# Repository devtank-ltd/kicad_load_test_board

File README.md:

# kicad_load_test_board
A software controlled load test board for resistive load testing of products

Copyright Devtank Ltd 2019.

This documentation describes Open Hardware and is licensed under the CERN OHL v. 1.2.
You may redistribute and modify this documentation under the terms of the CERN OHL v.1.2. (http://ohwr.org/cernohl). This documentation is distributed WITHOUT ANY EXPRESS OR IMPLIED WARRANTY, INCLUDING OF MERCHANTABILITY, SATISFACTORY QUALITY AND FITNESS FOR A PARTICULAR PURPOSE. Please see the CERN OHL v.1.2 for applicable conditions

This folder contains the load test board hardware schematics and pcb layout files 

You will need Kicad to open hardware design files.

Test and measurement products can be purchased directly from Devtank Ltd.

Please contact:
Tim Telford
Technical Director - Devtank Ltd
+44 (0)1335 818014

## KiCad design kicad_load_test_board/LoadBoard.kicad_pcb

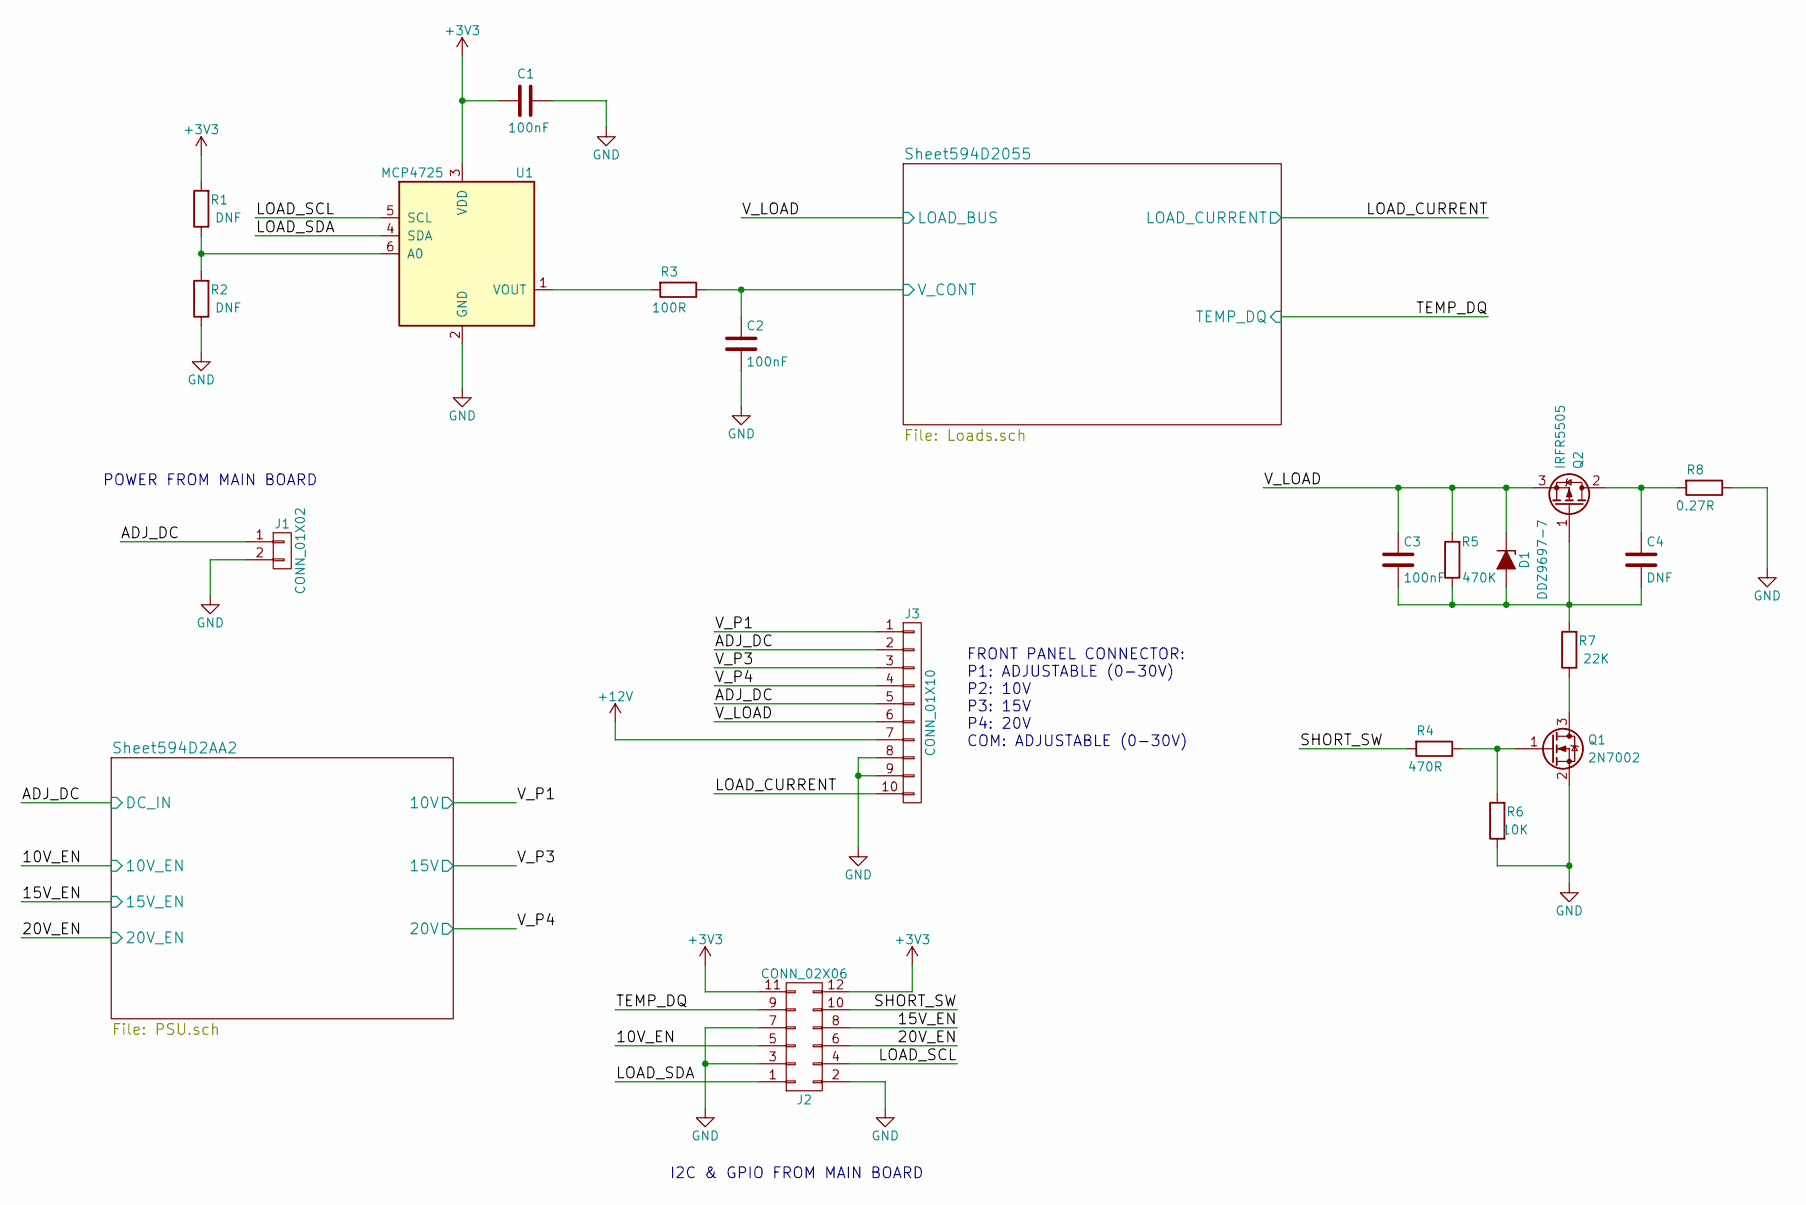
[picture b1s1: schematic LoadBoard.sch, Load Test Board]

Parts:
C1, C2, C3: 100nF; C_0603
C4: DNF; C_0603
D1: DDZ9697-7; D_SOD-123
J1: CONN_01X02; Molex_MiniFit-JR-5556-02A_2x01x4.20mm_Straight
J2: CONN_02X06; IDC_Header_Straight_12pins
J3: CONN_01X10; Molex_KK-6410-10_10x2.54mm_Straight
Q1: 2N7002; SOT-23
Q2: IRFR5505; TO-252-3_TabPin2
R1, R2: DNF; R_0603
R3: 100R; R_0603
R4: 470R; R_0603
R5: 470K; R_0603
R6: 10K; R_0603
R7: 22K; R_0603
R8: 0.27R; R_2816
U1: MCP4725; SOT-23-6

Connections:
+3V3: C1.2, J2.11, J2.12, R1.2, U1.3 (VDD); also elsewhere on the board
+12V: J3.7; also elsewhere on the board
/10V_EN: J2.5; also elsewhere on the board
/15V_EN: J2.8; also elsewhere on the board
/20V_EN: J2.6; also elsewhere on the board
/ADJ_DC: J1.1, J3.2, J3.5; also elsewhere on the board
/LOAD_CURRENT: J3.10; also elsewhere on the board
/LOAD_SCL: J2.4, U1.5 (SCL)
/LOAD_SDA: J2.1, U1.4 (SDA)
/SHORT_SW: J2.10, R4.2
/Sheet594D2055/V_CONT: C2.1, R3.1; also elsewhere on the board
/TEMP_DQ: J2.9; also elsewhere on the board
/V_LOAD: C3.1, D1.1 (K), J3.6, Q2.3 (S), R5.2; also elsewhere on the board
/V_P1: J3.1; also elsewhere on the board
/V_P3: J3.3; also elsewhere on the board
/V_P4: J3.4; also elsewhere on the board
GND: C1.1, C2.2, J1.2, J2.2, J2.3, J2.7, J3.8, J3.9, Q1.2 (S), R2.1, R6.1, R8.1, U1.2 (GND); also elsewhere on the board
unnamed: C3.2, C4.2, D1.2 (A), Q2.1 (G), R5.1, R7.2
unnamed: C4.1, Q2.2 (D), R8.2
unnamed: Q1.1 (G), R4.1, R6.2
unnamed: Q1.3 (D), R7.1
unnamed: R1.1, R2.2, U1.6 (A0)
unnamed: R3.2, U1.1 (VOUT)

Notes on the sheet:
POWER FROM MAIN BOARD
I2C & GPIO FROM MAIN BOARD
FRONT PANEL CONNECTOR: P1: ADJUSTABLE (0-30V) P2: 10V P3: 15V P4: 20V COM: ADJUSTABLE (0-30V)

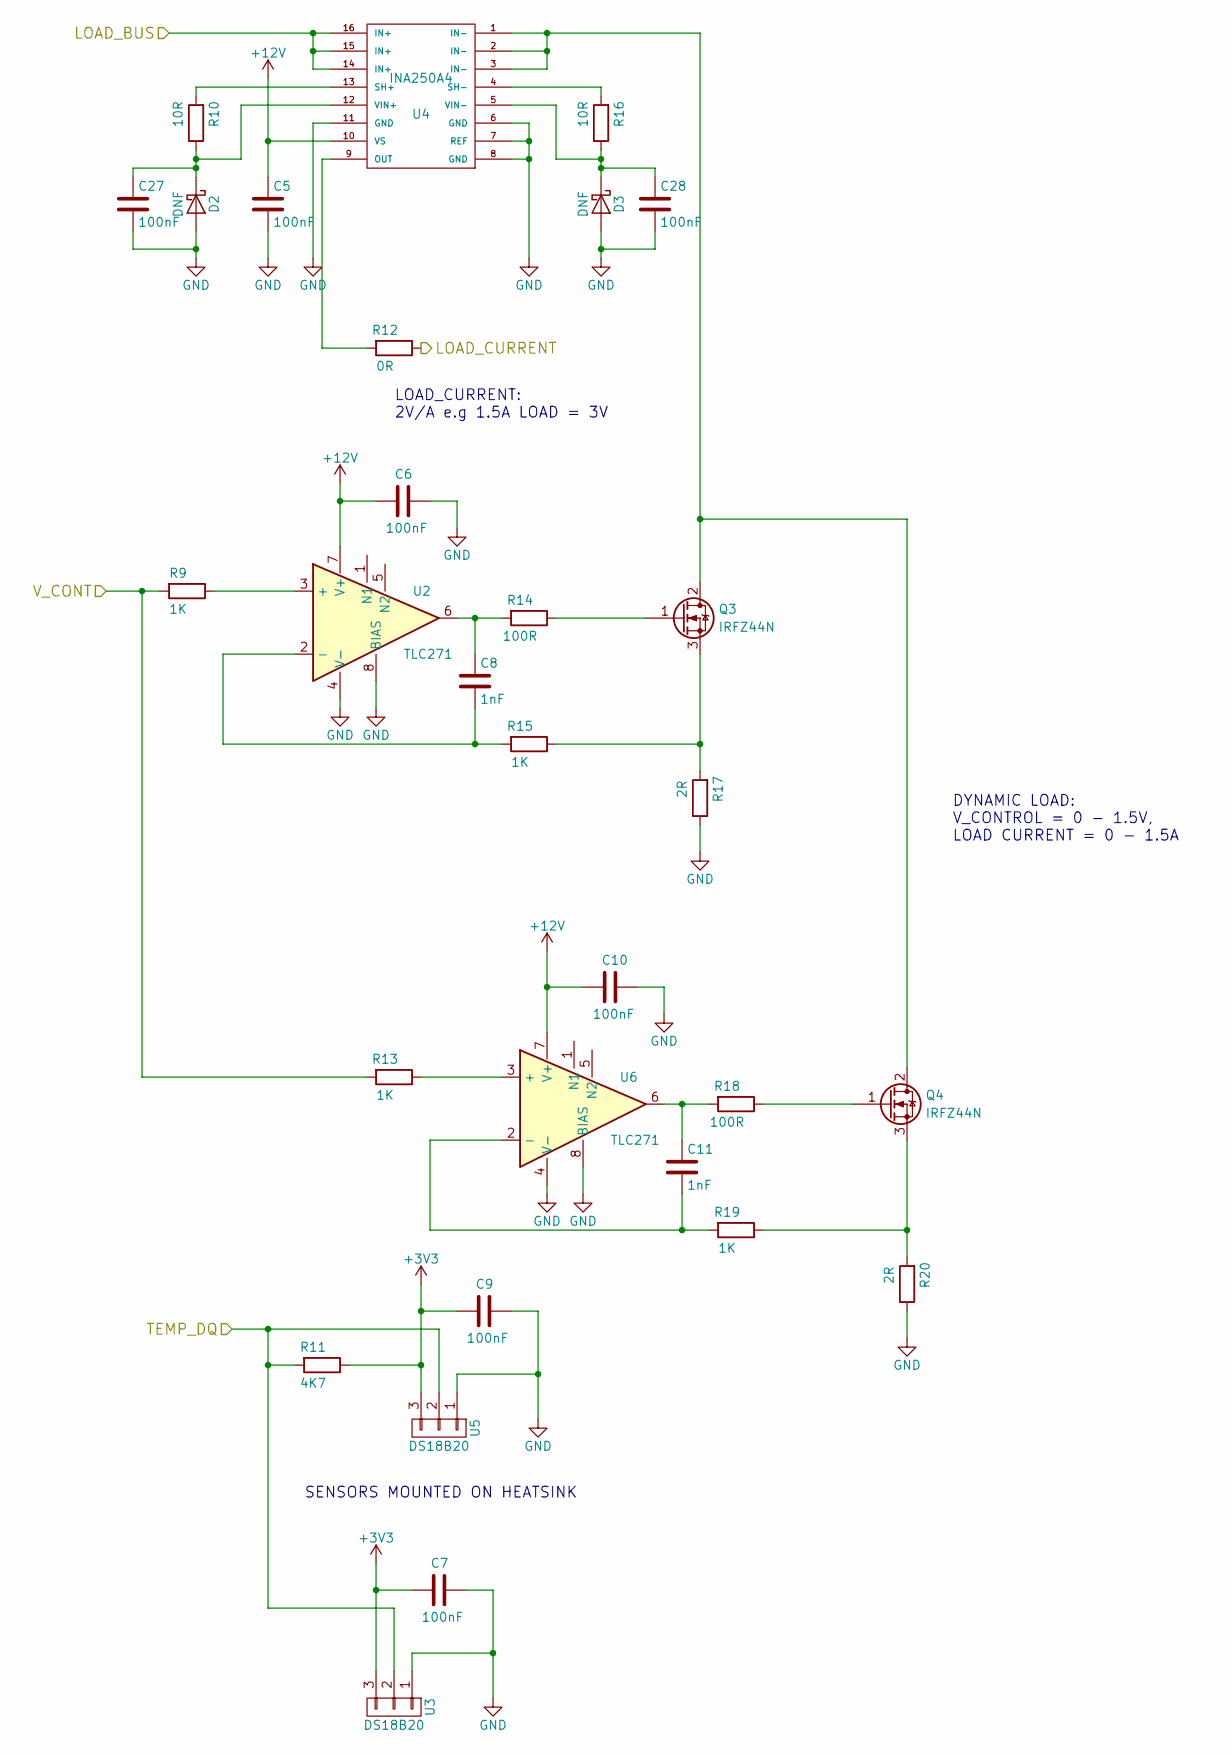
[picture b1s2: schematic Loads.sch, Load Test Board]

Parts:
C5, C6, C7, C9, C10, C27, C28: 100nF; C_0603
C8, C11: 1nF; C_0603
D2, D3: DNF; D_SOD-123
Q3, Q4: IRFZ44N; TO-220_Vertical
R9, R13, R15, R19: 1K; R_0603
R10, R16: 10R; R_0603
R11: 4K7; R_0603
R12: 0R; R_0603
R14, R18: 100R; R_0603
R17, R20: 2R; R_4527
U2, U6: TLC271; SOIC-8_3.9x4.9mm_Pitch1.27mm
U3, U5: DS18B20; TO-92_Inline_Narrow_Oval
U4: INA250A4; TSSOP-16_4.4x5mm_Pitch0.65mm

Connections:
+3V3: C7.2, C9.2, R11.1, U3.3, U5.3; also elsewhere on the board
+12V: C5.1, C6.2, C10.2, U2.7 (V+), U4.10 (VS), U6.7 (V+); also elsewhere on the board
/LOAD_CURRENT: R12.1; also elsewhere on the board
/Sheet594D2055/V_CONT: R9.2, R13.2; also elsewhere on the board
/TEMP_DQ: R11.2, U3.2, U5.2; also elsewhere on the board
/V_LOAD: U4.14 (IN+), U4.15 (IN+), U4.16 (IN+); also elsewhere on the board
GND: C5.2, C6.1, C7.1, C9.1, C10.1, C27.2, C28.2, D2.2 (A), D3.2 (A), R17.1, R20.1, U2.4 (V-), U2.8 (BIAS), U3.1, U4.6 (GND), U4.7 (REF), U4.8 (GND), U4.11 (GND), U5.1, U6.4 (V-), U6.8 (BIAS); also elsewhere on the board
unnamed: C8.1, R14.2, U2.6
unnamed: C8.2, R15.2, U2.2 (-)
unnamed: C11.1, R18.2, U6.6
unnamed: C11.2, R19.2, U6.2 (-)
unnamed: C27.1, D2.1 (K), R10.1, U4.12 (VIN+)
unnamed: C28.1, D3.1 (K), R16.1, U4.5 (VIN-)
unnamed: Q3.1 (G), R14.1
unnamed: Q3.2 (D), Q4.2 (D), U4.1 (IN-), U4.2 (IN-), U4.3 (IN-)
unnamed: Q3.3 (S), R15.1, R17.2
unnamed: Q4.1 (G), R18.1
unnamed: Q4.3 (S), R19.1, R20.2
unnamed: R9.1, U2.3 (+)
unnamed: R10.2, U4.13 (SH+)
unnamed: R12.2, U4.9 (OUT)
unnamed: R13.1, U6.3 (+)
unnamed: R16.2, U4.4 (SH-)

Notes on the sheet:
DYNAMIC LOAD: V_CONTROL = 0 - 1.5V, LOAD CURRENT = 0 - 1.5A
LOAD_CURRENT: 2V/A e.g 1.5A LOAD = 3V
SENSORS MOUNTED ON HEATSINK

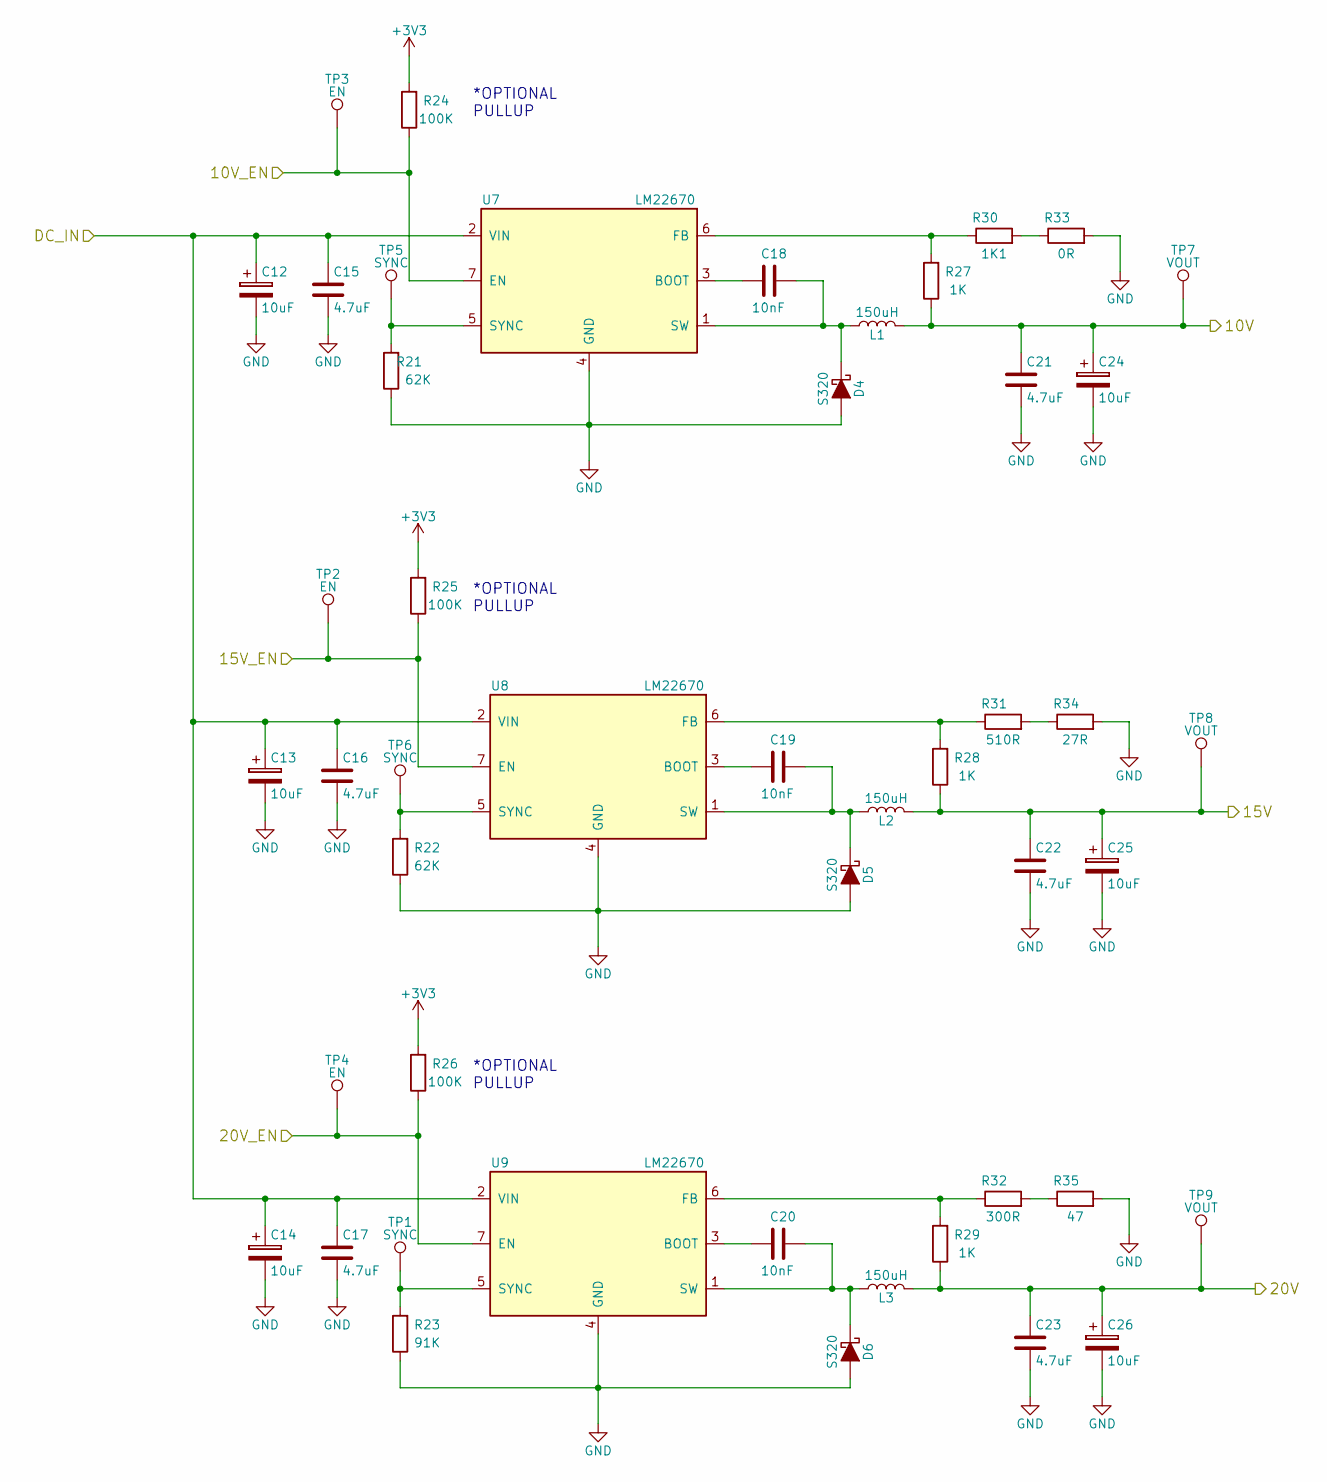
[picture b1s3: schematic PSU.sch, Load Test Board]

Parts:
C12, C13, C14, C24, C25, C26: 10uF; CP_Elec_6.3x7.7
C15, C16, C17, C21, C22, C23: 4.7uF; C_1210
C18, C19, C20: 10nF; C_0603
D4, D5, D6: S320; D_SMB
L1, L2, L3: 150uH; Inductor_13x13
R21, R22: 62K; R_0603
R23: 91K; R_0603
R24, R25, R26: 100K; R_0603
R27, R28, R29: 1K; R_0603
R30: 1K1; R_0603
R31: 510R; R_0603
R32: 300R; R_0603
R33: 0R; R_0603
R34: 27R; R_0603
R35: 47; R_0603
TP1, TP5, TP6: SYNC; Measurement_Point_Round-TH_Small
TP2, TP3, TP4: EN; Measurement_Point_Round-TH_Small
TP7, TP8, TP9: VOUT; Measurement_Point_Round-TH_Small
U7, U8, U9: LM22670; TO-263-7_TabPin4

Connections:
+3V3: R24.2, R25.2, R26.2; also elsewhere on the board
/10V_EN: R24.1, TP3.1, U7.7 (EN); also elsewhere on the board
/15V_EN: R25.1, TP2.1, U8.7 (EN); also elsewhere on the board
/20V_EN: R26.1, TP4.1, U9.7 (EN); also elsewhere on the board
/ADJ_DC: C12.1, C13.1, C14.1, C15.1, C16.1, C17.1, U7.2 (VIN), U8.2 (VIN), U9.2 (VIN); also elsewhere on the board
/V_P1: C21.1, C24.1, L1.2, R27.1, TP7.1; also elsewhere on the board
/V_P3: C22.1, C25.1, L2.2, R28.1, TP8.1; also elsewhere on the board
/V_P4: C23.1, C26.1, L3.2, R29.1, TP9.1; also elsewhere on the board
GND: C12.2, C13.2, C14.2, C15.2, C16.2, C17.2, C21.2, C22.2, C23.2, C24.2, C25.2, C26.2, D4.2 (A), D5.2 (A), D6.2 (A), R21.1, R22.1, R23.1, R33.2, R34.2, R35.2, U7.4 (GND), U8.4 (GND), U9.4 (GND); also elsewhere on the board
unnamed: C18.1, D4.1 (K), L1.1, U7.1 (SW)
unnamed: C18.2, U7.3 (BOOT)
unnamed: C19.1, D5.1 (K), L2.1, U8.1 (SW)
unnamed: C19.2, U8.3 (BOOT)
unnamed: C20.1, D6.1 (K), L3.1, U9.1 (SW)
unnamed: C20.2, U9.3 (BOOT)
unnamed: R21.2, TP5.1, U7.5 (SYNC)
unnamed: R22.2, TP6.1, U8.5 (SYNC)
unnamed: R23.2, TP1.1, U9.5 (SYNC)
unnamed: R27.2, R30.1, U7.6 (FB)
unnamed: R28.2, R31.1, U8.6 (FB)
unnamed: R29.2, R32.1, U9.6 (FB)
unnamed: R30.2, R33.1
unnamed: R31.2, R34.1
unnamed: R32.2, R35.1

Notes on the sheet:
*OPTIONAL PULLUP

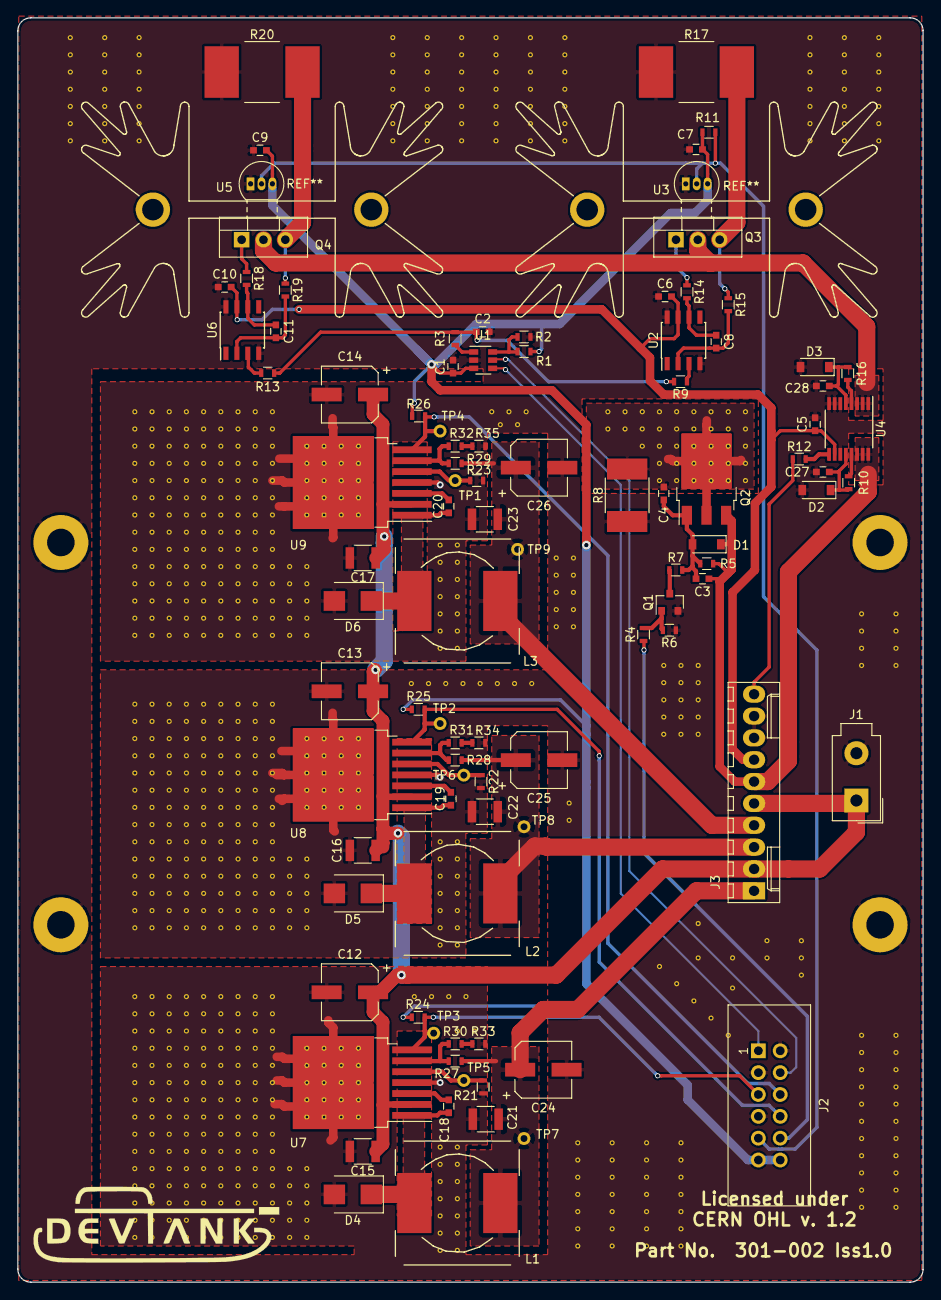
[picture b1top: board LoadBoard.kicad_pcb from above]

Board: 2 copper layers, 105.2 x 147.0 mm, 97 parts (0 on the bottom side), 54 nets.

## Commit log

2019-07-03 Setup common library files
2019-07-03 Add KiCAD project files
2019-07-03 add readme
2019-07-03 update common to relative path
2019-07-03 copied legacy project to new git repo
2019-07-03 house keeping documents
